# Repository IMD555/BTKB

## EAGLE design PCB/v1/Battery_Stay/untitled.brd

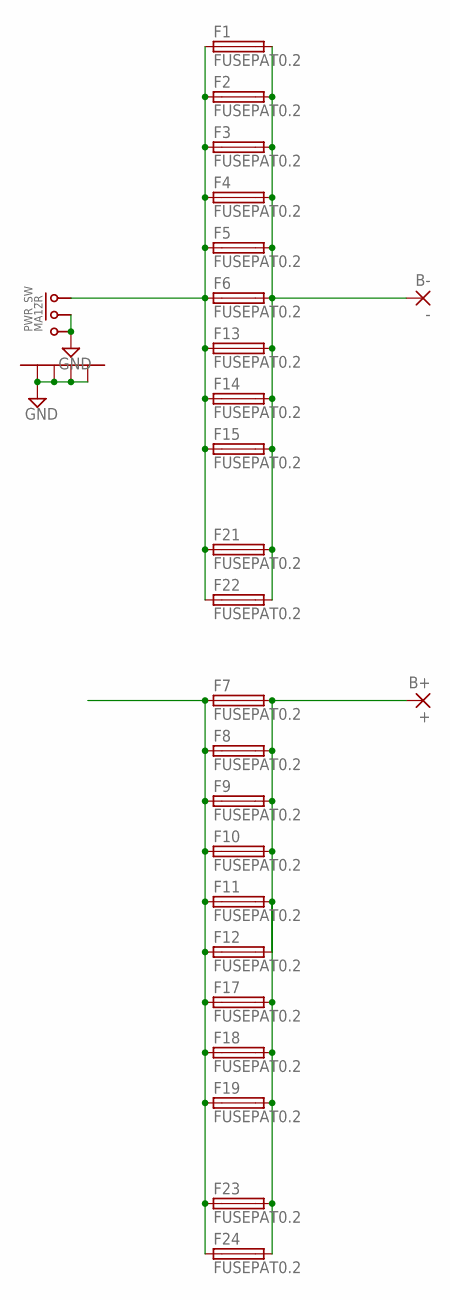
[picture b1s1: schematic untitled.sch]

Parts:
B+: +; SMD2,5-5
B-: -; SMD2,5-5
F1, F2, F3, F4, F5, F6, F7, F8, F9, F10, F11, F12, F13, F14, F15, F17, F18, F19, F21, F22, F23, F24: FUSEPAT0.2; FUSE_PAT1
PWR_SW: MA12R

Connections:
GND: PWR_SW.P$2 (2), PWR_SW.P$3 (3), PWR_SW.P$4, PWR_SW.P$5, PWR_SW.P$6, PWR_SW.P$7
unnamed: F1.P$1 (1), F2.P$1 (1), F3.P$1 (1), F4.P$1 (1), F5.P$1 (1), F6.P$1 (1), F13.P$1 (1), F14.P$1 (1), F15.P$1 (1), F21.P$1 (1), F22.P$1 (1), PWR_SW.P$1 (1)
unnamed: B-.1, F1.P$2 (2), F2.P$2 (2), F3.P$2 (2), F4.P$2 (2), F5.P$2 (2), F6.P$2 (2), F13.P$2 (2), F14.P$2 (2), F15.P$2 (2), F21.P$2 (2), F22.P$2 (2)
unnamed: F7.P$1 (1), F8.P$1 (1), F9.P$1 (1), F10.P$1 (1), F11.P$1 (1), F12.P$1 (1), F17.P$1 (1), F18.P$1 (1), F19.P$1 (1), F23.P$1 (1), F24.P$1 (1)
unnamed: B+.1, F7.P$2 (2), F8.P$2 (2), F9.P$2 (2), F10.P$2 (2), F11.P$2 (2), F12.P$2 (2), F17.P$2 (2), F18.P$2 (2), F19.P$2 (2), F23.P$2 (2), F24.P$2 (2)

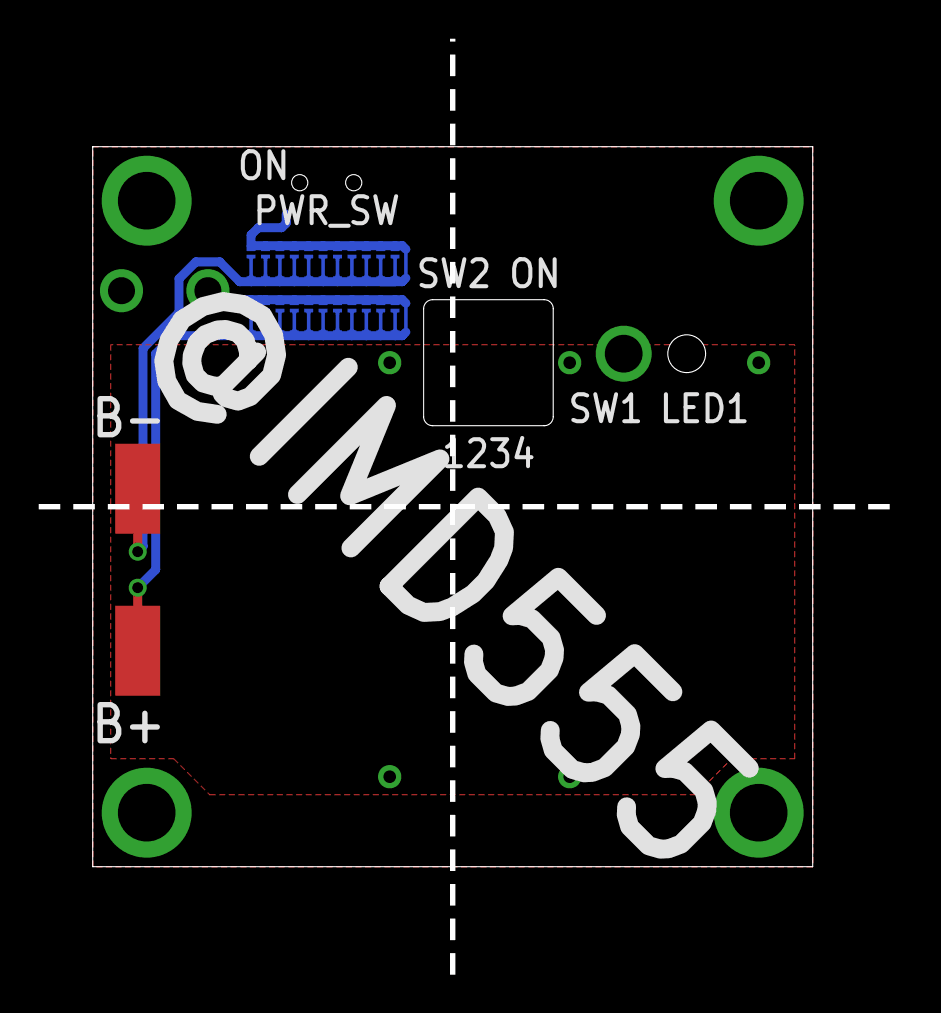
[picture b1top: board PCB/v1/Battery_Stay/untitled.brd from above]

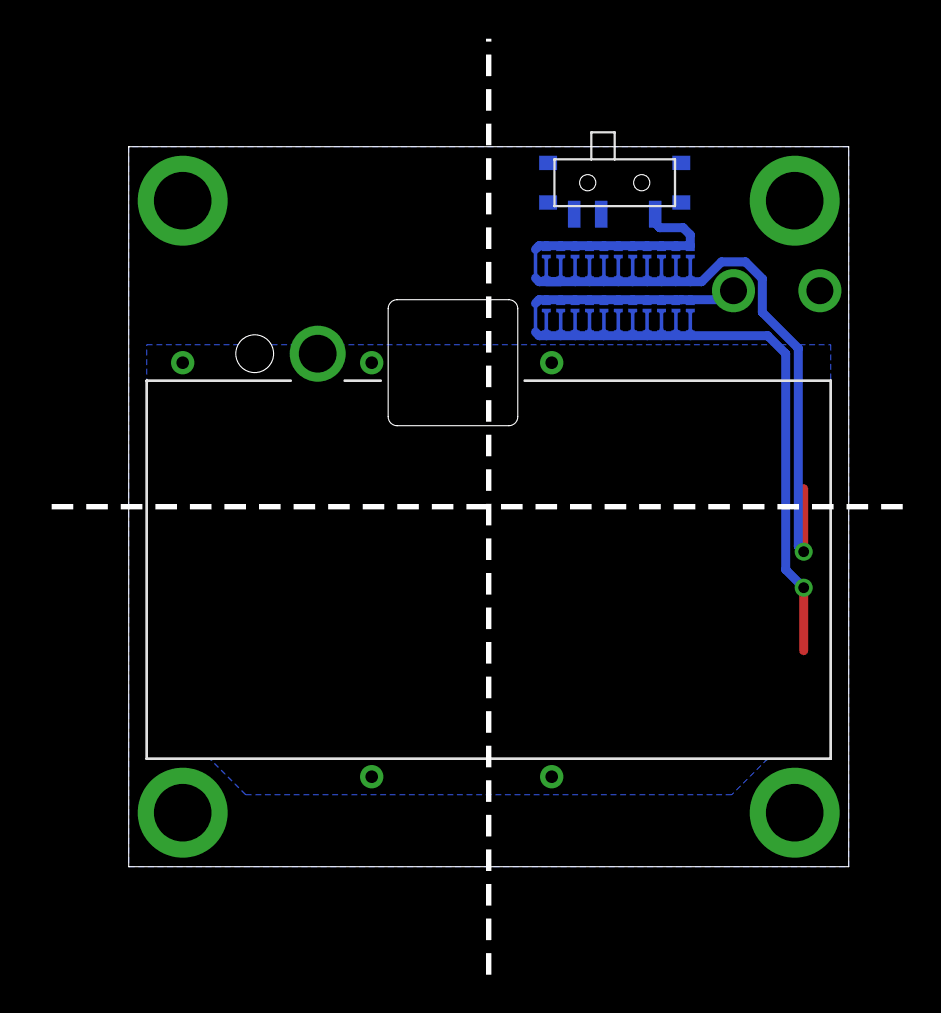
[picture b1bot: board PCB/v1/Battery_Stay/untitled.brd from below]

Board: 2 copper layers, 48.0 x 52.0 mm, 25 parts (23 on the bottom side), 5 nets.

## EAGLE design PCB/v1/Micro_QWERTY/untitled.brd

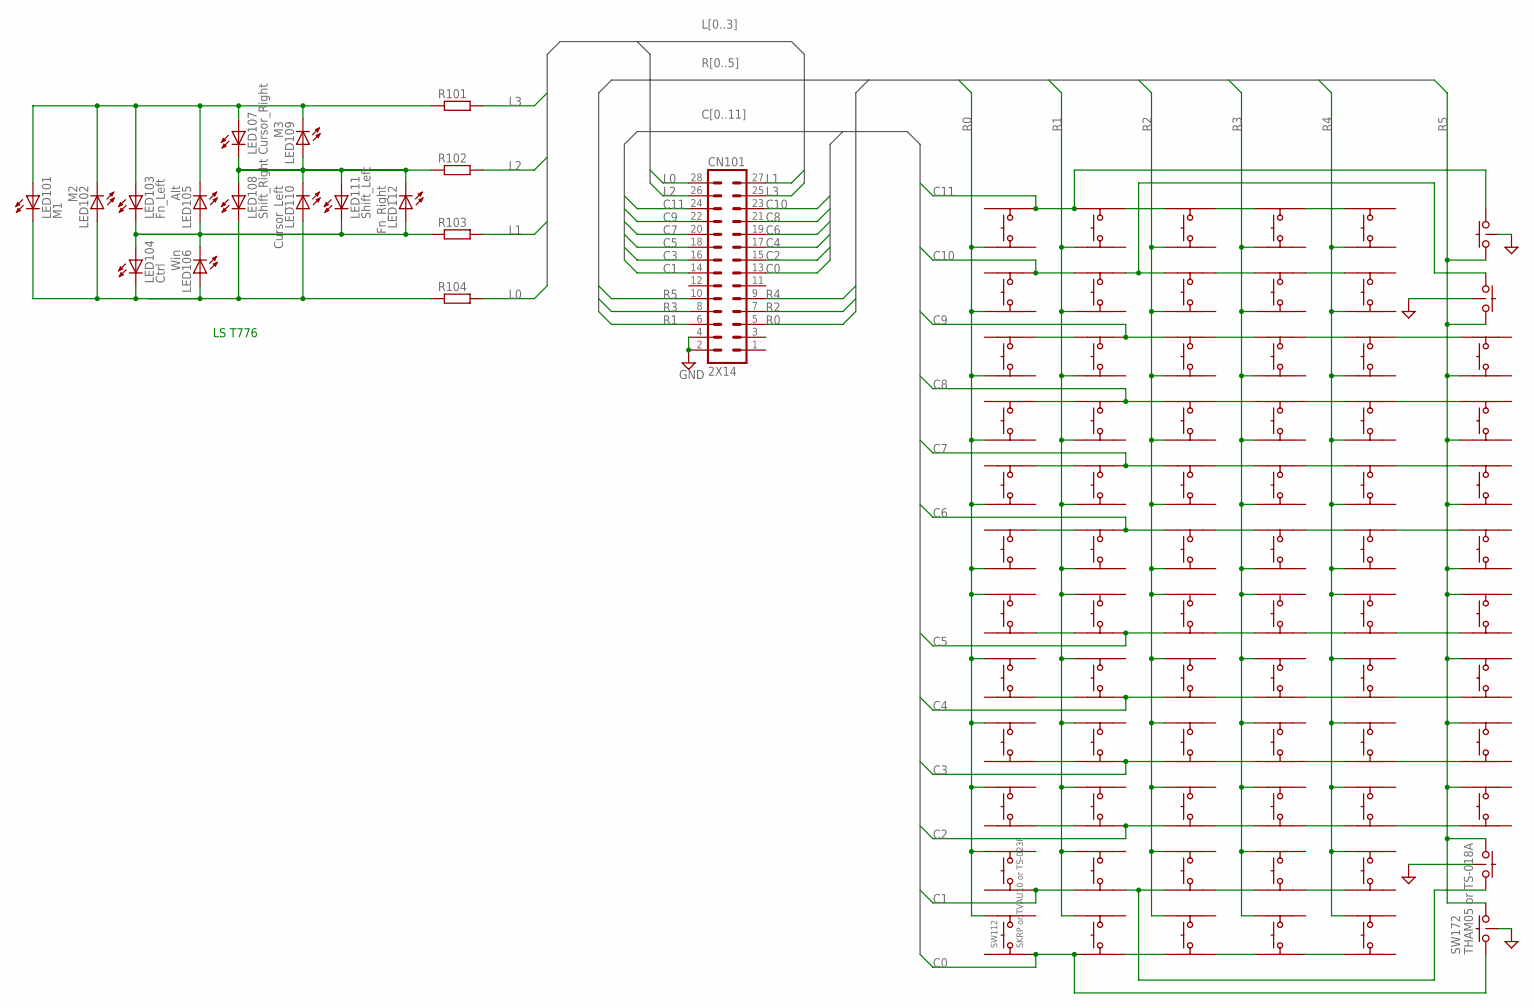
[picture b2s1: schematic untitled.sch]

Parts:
CN101: 2X14; 2MM_14X2
LED101: M1; P-LCC-2-TOPLED-RG
LED102: M2; P-LCC-2-TOPLED-RG
LED103: Fn_Left; P-LCC-2-TOPLED-RG
LED104: Ctrl; P-LCC-2-TOPLED-RG
LED105: Alt; P-LCC-2-TOPLED-RG
LED106: Win; P-LCC-2-TOPLED-RG
LED107: Cursor_Right; P-LCC-2-TOPLED-RG
LED108: Shift_Right; P-LCC-2-TOPLED-RG
LED109: M3; P-LCC-2-TOPLED-RG
LED110: Cursor_Left; P-LCC-2-TOPLED-RG
LED111: Shift_Left; P-LCC-2-TOPLED-RG
LED112: Fn_Right; P-LCC-2-TOPLED-RG
R101, R102, R103, R104: R-EU_R0402-SS; R0402-SS
SW101, SW102, SW103, SW104, SW105, SW106, SW107, SW108, SW109, SW110, SW111, SW113, SW114, SW115, SW116, SW117, SW118, SW119, SW120, SW121, SW122, SW123, SW124, SW125, SW126, SW127, SW128, SW129, SW130, SW131, SW132, SW133, SW134, SW135, SW136, SW137, SW138, SW139, SW140, SW141, SW142, SW143, SW144, SW145, SW146, SW147, SW148, SW149, SW150, SW151, SW152, SW153, SW154, SW155, SW156, SW157, SW158, SW159, SW160, SW163, SW164, SW165, SW166, SW167, SW168, SW169, SW170: SW_4PTVAU10-025; TVAU10-025
SW112: SKRP or TVAU10 or TS-023F; TVAU10-025
SW161, SW162, SW171: SW_WITH_EARTHX; THAM05
SW172: THAM05 or TS-018A; THAM05

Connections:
C0: CN101.13, SW112.P$2 (=A), SW124.P$1 (A), SW172.P$1
C1: CN101.14, SW111.P$2 (=A), SW123.P$1 (A)
C2: CN101.15, SW122.P$2 (=A), SW134.P$1 (A)
C3: CN101.16, SW121.P$2 (=A), SW133.P$1 (A)
C4: CN101.17, SW120.P$2 (=A), SW132.P$1 (A)
C5: CN101.18, SW119.P$2 (=A), SW131.P$1 (A)
C6: CN101.19, SW118.P$4 (=B), SW130.P$3 (B)
C7: CN101.20, SW117.P$4 (=B), SW129.P$3 (B)
C8: CN101.21, SW116.P$4 (=B), SW128.P$3 (B)
C9: CN101.22, SW115.P$4 (=B), SW127.P$3 (B)
C10: CN101.23, SW102.P$4 (=B), SW114.P$3 (B)
C11: CN101.24, SW101.P$4 (=B), SW113.P$3 (B), SW161.P$2
GND: CN101.2, CN101.4, SW161.S1, SW161.S2, SW161.S3, SW161.S4, SW161.S5, SW162.S1, SW162.S2, SW162.S3, SW162.S4, SW162.S5, SW171.S1, SW171.S2, SW171.S3, SW171.S4, SW171.S5, SW172.S1, SW172.S2, SW172.S3, SW172.S4, SW172.S5
L0: CN101.28, R104.2
L1: CN101.27, R103.2
L2: CN101.26, R102.2
L3: CN101.25, R101.2
unnamed: LED107.C, LED108.A, LED109.A, LED110.C, LED111.A, LED112.C, R102.1
unnamed: LED101.A, LED102.C, LED103.A, LED105.C, LED107.A, LED109.C, R101.1
unnamed: LED103.C, LED104.A, LED105.A, LED106.C, LED111.C, LED112.A, R103.1
unnamed: LED101.C, LED102.A, LED104.C, LED106.A, LED108.C, LED110.A, R104.1
unnamed: SW123.P$2 (=A), SW135.P$1 (A), SW171.P$2
unnamed: SW113.P$4 (=B), SW125.P$3 (B)
unnamed: SW114.P$4 (=B), SW126.P$3 (B), SW162.P$1
unnamed: SW106.P$4 (=B), SW118.P$3 (B)
unnamed: SW130.P$4 (=B), SW142.P$3 (B)
unnamed: SW154.P$4 (=B), SW166.P$3 (B)
unnamed: SW142.P$4 (=B), SW154.P$3 (B)
unnamed: SW105.P$4 (=B), SW117.P$3 (B)
unnamed: SW129.P$4 (=B), SW141.P$3 (B)
unnamed: SW153.P$4 (=B), SW165.P$3 (B)
unnamed: SW141.P$4 (=B), SW153.P$3 (B)
unnamed: SW104.P$4 (=B), SW116.P$3 (B)
unnamed: SW128.P$4 (=B), SW140.P$3 (B)
unnamed: SW152.P$4 (=B), SW164.P$3 (B)
unnamed: SW140.P$4 (=B), SW152.P$3 (B)
unnamed: SW103.P$4 (=B), SW115.P$3 (B)
unnamed: SW127.P$4 (=B), SW139.P$3 (B)
unnamed: SW151.P$4 (=B), SW163.P$3 (B)
unnamed: SW139.P$4 (=B), SW151.P$3 (B)
unnamed: SW126.P$4 (=B), SW138.P$3 (B)
unnamed: SW138.P$4 (=B), SW150.P$3 (B)
unnamed: SW125.P$4 (=B), SW137.P$3 (B)
unnamed: SW137.P$4 (=B), SW149.P$3 (B)
unnamed: SW107.P$2 (=A), SW119.P$1 (A)
unnamed: SW131.P$2 (=A), SW143.P$1 (A)
unnamed: SW155.P$2 (=A), SW167.P$1 (A)
unnamed: SW143.P$2 (=A), SW155.P$1 (A)
unnamed: SW108.P$2 (=A), SW120.P$1 (A)
unnamed: SW132.P$2 (=A), SW144.P$1 (A)
unnamed: SW156.P$2 (=A), SW168.P$1 (A)
unnamed: SW144.P$2 (=A), SW156.P$1 (A)
unnamed: SW109.P$2 (=A), SW121.P$1 (A)
unnamed: SW133.P$2 (=A), SW145.P$1 (A)
unnamed: SW157.P$2 (=A), SW169.P$1 (A)
unnamed: SW145.P$2 (=A), SW157.P$1 (A)
unnamed: SW110.P$2 (=A), SW122.P$1 (A)
unnamed: SW134.P$2 (=A), SW146.P$1 (A)
unnamed: SW158.P$2 (=A), SW170.P$1 (A)
unnamed: SW146.P$2 (=A), SW158.P$1 (A)
unnamed: SW135.P$2 (=A), SW147.P$1 (A)
unnamed: SW147.P$2 (=A), SW159.P$1 (A)
unnamed: SW124.P$2 (=A), SW136.P$1 (A)
unnamed: SW136.P$2 (=A), SW148.P$1 (A)
unnamed: SW148.P$2 (=A), SW160.P$1 (A)
R0: CN101.5, SW101.P$1 (A), SW102.P$1 (A), SW103.P$1 (A), SW104.P$1 (A), SW105.P$1 (A), SW106.P$1 (A), SW107.P$3 (B), SW108.P$3 (B), SW109.P$3 (B), SW110.P$3 (B), SW111.P$3 (B), SW112.P$3 (B)
R1: CN101.6, SW113.P$1 (A), SW114.P$1 (A), SW115.P$1 (A), SW116.P$1 (A), SW117.P$1 (A), SW118.P$1 (A), SW119.P$3 (B), SW120.P$3 (B), SW121.P$3 (B), SW122.P$3 (B), SW123.P$3 (B), SW124.P$3 (B)
R2: CN101.7, SW125.P$1 (A), SW126.P$1 (A), SW127.P$1 (A), SW128.P$1 (A), SW129.P$1 (A), SW130.P$1 (A), SW131.P$3 (B), SW132.P$3 (B), SW133.P$3 (B), SW134.P$3 (B), SW135.P$3 (B), SW136.P$3 (B)
R3: CN101.8, SW137.P$1 (A), SW138.P$1 (A), SW139.P$1 (A), SW140.P$1 (A), SW141.P$1 (A), SW142.P$1 (A), SW143.P$3 (B), SW144.P$3 (B), SW145.P$3 (B), SW146.P$3 (B), SW147.P$3 (B), SW148.P$3 (B)
R4: CN101.9, SW149.P$1 (A), SW150.P$1 (A), SW151.P$1 (A), SW152.P$1 (A), SW153.P$1 (A), SW154.P$1 (A), SW155.P$3 (B), SW156.P$3 (B), SW157.P$3 (B), SW158.P$3 (B), SW159.P$3 (B), SW160.P$3 (B)
R5: CN101.10, SW161.P$1, SW162.P$2, SW163.P$1 (A), SW164.P$1 (A), SW165.P$1 (A), SW166.P$1 (A), SW167.P$3 (B), SW168.P$3 (B), SW169.P$3 (B), SW170.P$3 (B), SW171.P$1, SW172.P$2

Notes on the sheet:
LS T776

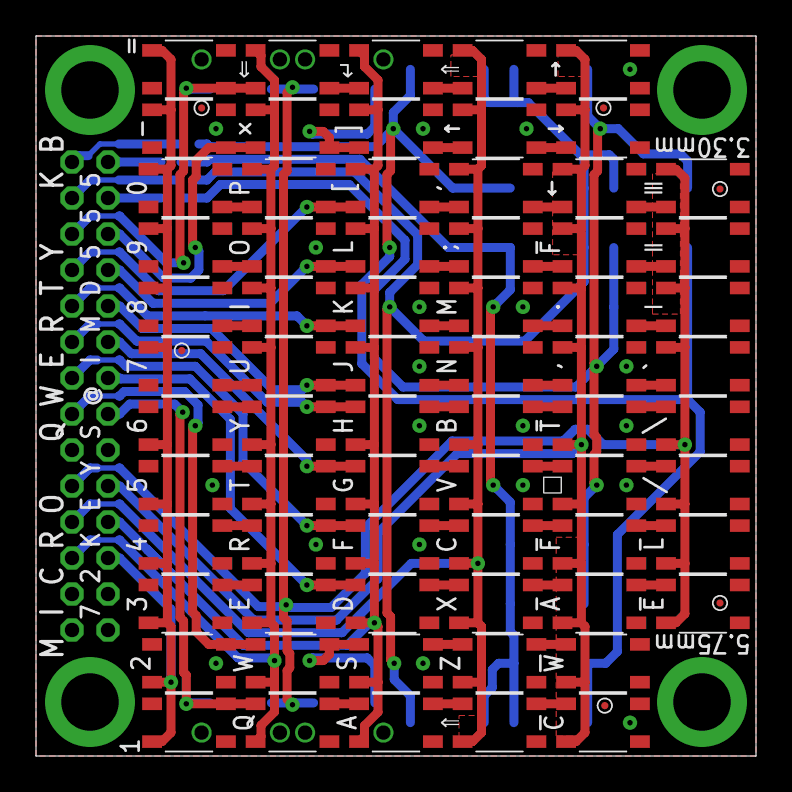
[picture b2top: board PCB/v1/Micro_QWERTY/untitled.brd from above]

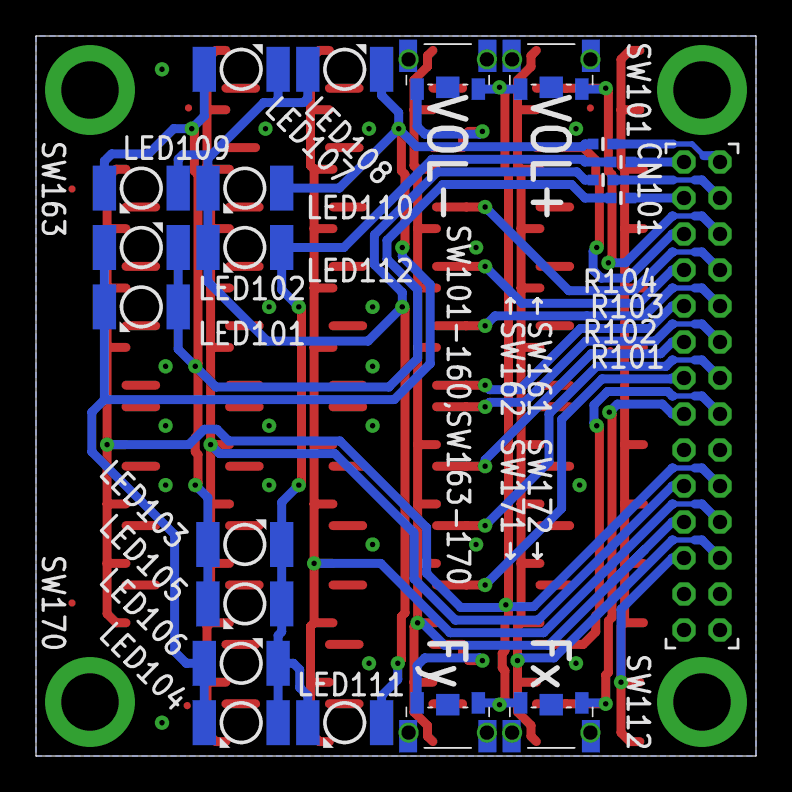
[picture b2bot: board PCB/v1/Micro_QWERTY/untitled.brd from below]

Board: 2 copper layers, 40.0 x 40.0 mm, 97 parts (22 on the bottom side), 71 nets.

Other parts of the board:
U$1, U$4, U$5, U$6, U$7, U$8: PCB_CHECK
U$2, U$3: RULER-S

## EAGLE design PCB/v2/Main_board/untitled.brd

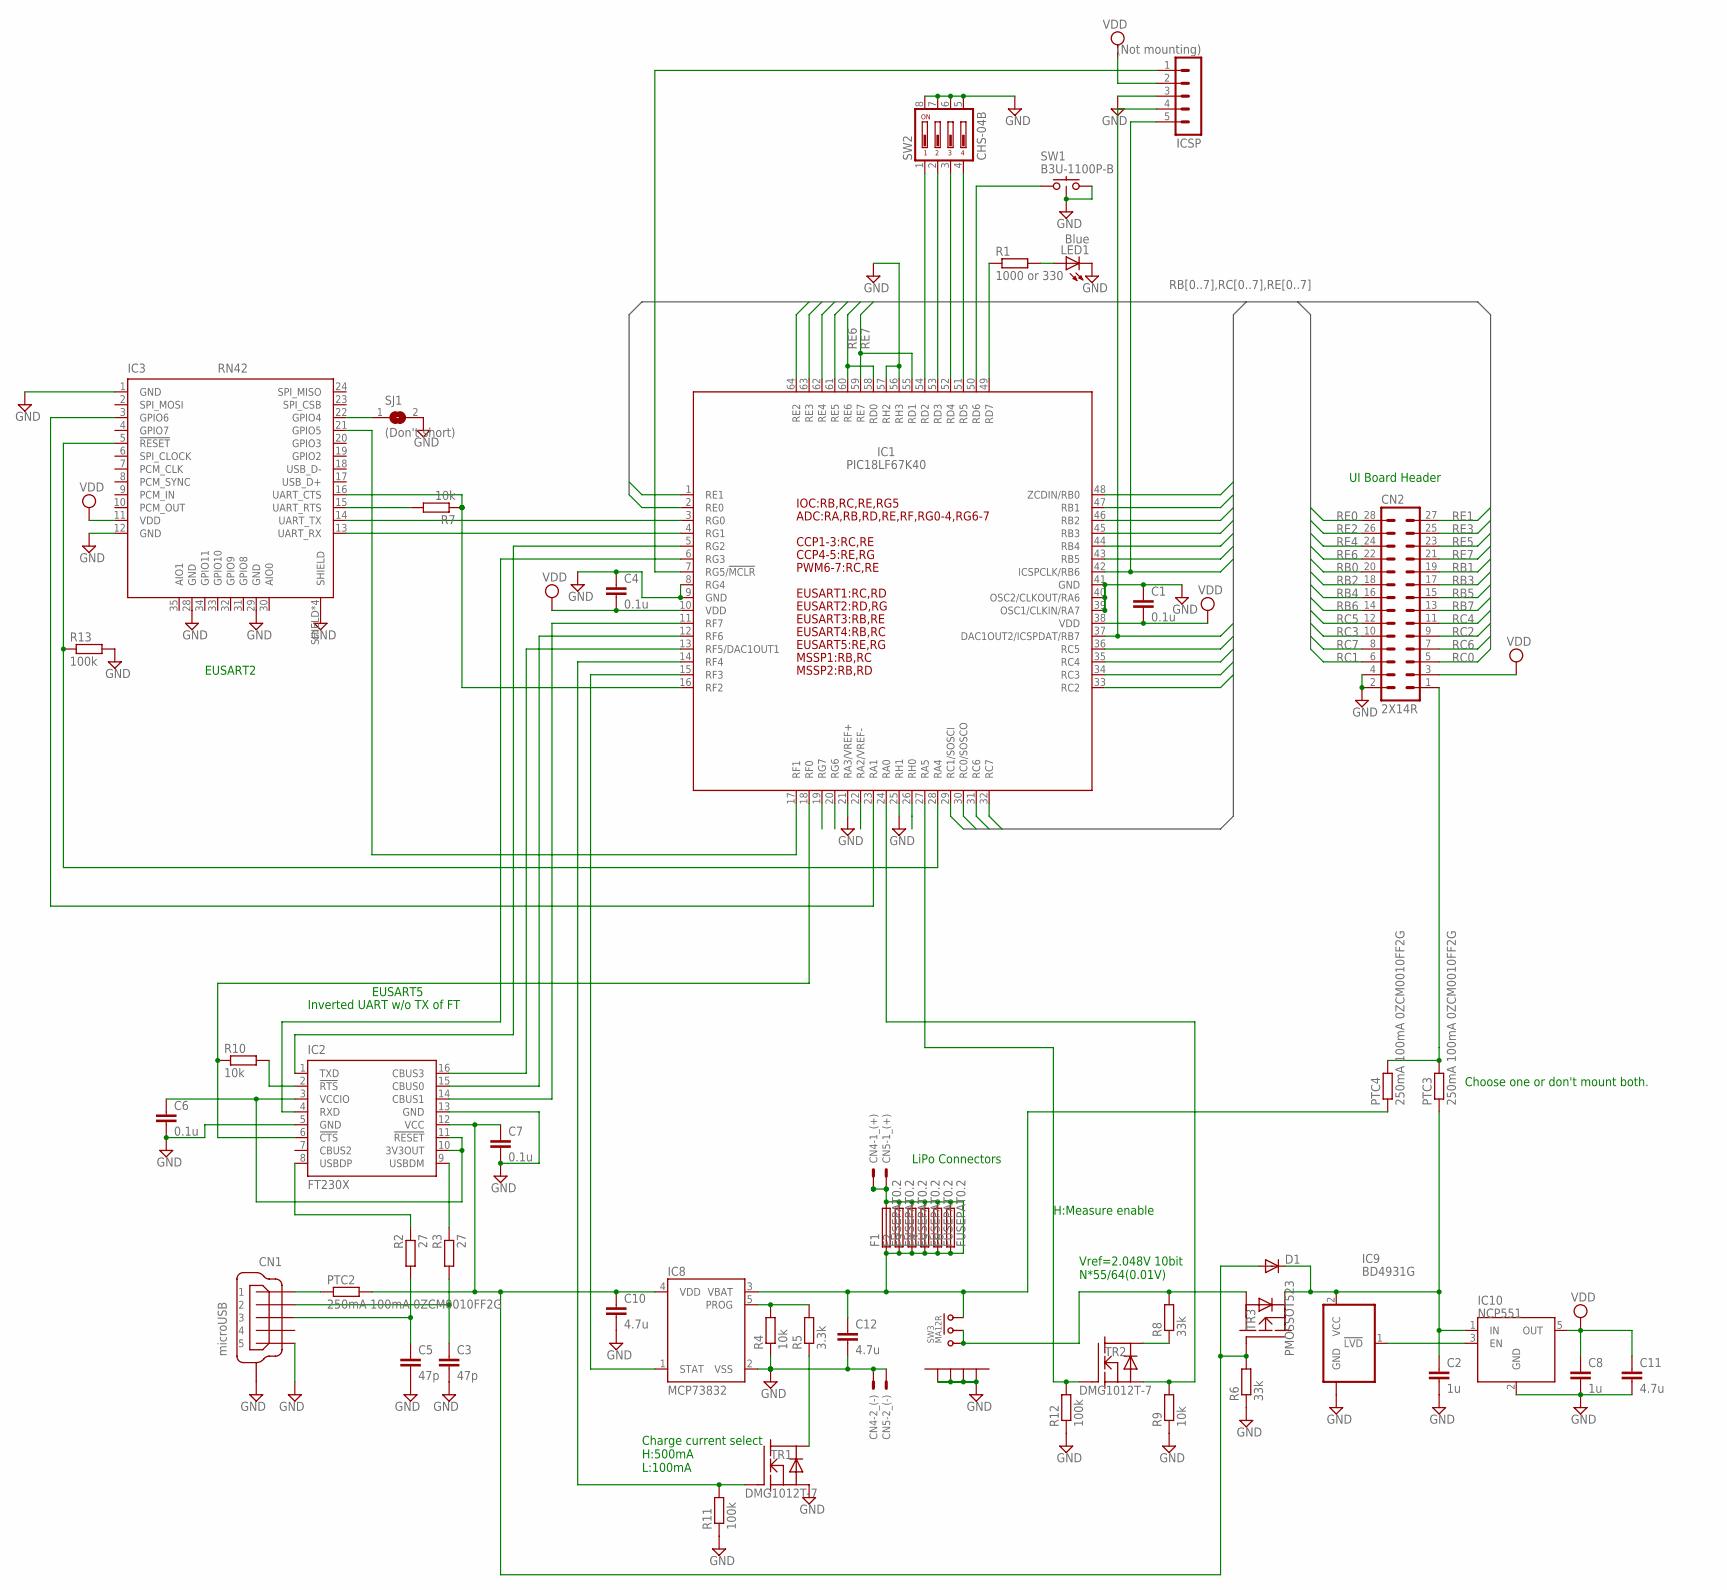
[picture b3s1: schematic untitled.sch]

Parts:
C1, C4, C6, C7: 0.1u; C0402-SS
C2, C8: 1u; C0805
C3, C5: 47p; C0402-SS
C10, C11, C12: 4.7u; C0805
CN1: microUSB; 10118194-0001LF
CN2: 2X14R; 2MM_14X2_R
CN4, CN5: 2P_(POWER)PH_S; PH-2_S
D1: DIODE-VMN2; VMN2
F1, F2, F3, F4, F5, F6: FUSEPAT0.2; FUSE_PAT1
IC1: PIC18LF67K40; TQFP64-10X10
IC2: FT230X; SSOP16
IC3: RN42; RN-42
IC8: MCP73832; SOT23-5L
IC9: BD4931G; SOT23-5L
IC10: NCP551; SOT23-5L
ICSP: (Not mounting); MA05-1
LED1: Blue; CHIP-LED1005
PTC2, PTC3, PTC4: 250mA 100mA 0ZCM0010FF2G; R0603
R1: 1000 or 330; R0402-SS
R2, R3: 27; R0402-SS
R4, R7, R9, R10: 10k; R0402-SS
R5: 3.3k; R0402-SS
R6, R8: 33k; R0402-SS
R11, R12, R13: 100k; R0402-SS
SJ1: (Don't short); SJ
SW1: B3U-1100P-B
SW2: CHS-04B
SW3: MA12R
TR1, TR2: DMG1012T-7; SOT523
TR3: PMOSSOT523; SOT523

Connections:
GND: C1.1, C2.2, C3.2, C4.1, C5.2, C6.2, C7.2, C8.2, C10.2, C11.2, C12.2, CN1.P$5 (5), CN1.P$6 (S), CN1.P$7 (S), CN1.S1 (S), CN1.S2 (S), CN1.S3 (S), CN1.S4 (S), CN1.S5 (S), CN1.S6 (S), CN1.S7 (S), CN1.S8 (S), CN1.S9 (S), CN1.S10 (S), CN2.2, CN2.4, CN4.2, CN5.2, IC1.8 (RG4), IC1.9 (GND), IC1.21 (RA3/VREF+), IC1.25 (RH1), IC1.39 (OSC1/CLKIN/RA7), IC1.40 (OSC2/CLKOUT/RA6), IC1.41 (GND), IC1.56 (RH3), IC1.57 (RH2), IC2.5 (GND), IC2.13 (GND), IC3.1 (GND), IC3.12 (GND), IC3.28 (GND), IC3.29 (GND), IC3.SHIELD, IC3.SHIELD@1 (SHIELD), IC3.SHIELD@2 (SHIELD), IC3.SHIELD@3 (SHIELD), IC8.2 (VSS), IC9.3 (GND), IC10.2 (GND), ICSP.3, LED1.C, R4.1, R6.1, R9.1, R11.1, R12.1, R13.2, SJ1.2, SW1.P$2, SW1.P$3, SW2.5, SW2.6, SW2.7, SW2.8, SW3.P$4, SW3.P$5, SW3.P$6, SW3.P$7, TR1.2 (S)
unnamed: IC1.4 (RG1), IC3.13 (UART_RX)
unnamed: IC1.5 (RG2), IC2.1 (TXD)
unnamed: IC1.3 (RG0), IC3.14 (UART_TX)
unnamed: C5.1, CN1.P$3 (3), R2.2
unnamed: C3.1, CN1.P$2 (2), R3.2
unnamed: IC1.6 (RG3), IC2.4 (RXD)
unnamed: CN2.1, PTC3.2, PTC4.2
unnamed: C7.1, C10.1, D1.A, IC2.12 (VCC), IC8.4 (VDD), PTC2.2, R6.2, TR3.1 (G)
unnamed: IC1.15 (RF3), IC8.1 (STAT)
unnamed: C12.1, CN4.1, CN5.1, F1.P$1 (1), F1.P$2 (2), F2.P$1 (1), F2.P$2 (2), F3.P$1 (1), F3.P$2 (2), F4.P$1 (1), F4.P$2 (2), F5.P$1 (1), F5.P$2 (2), F6.P$1 (1), F6.P$2 (2), IC8.3 (VBAT), PTC4.1, SW3.P$1 (1)
unnamed: R8.2, SW3.P$2 (2), SW3.P$3 (3), TR3.3 (D)
unnamed: IC1.7 (RG5/!MCLR), ICSP.1
unnamed: CN1.P$1 (1), PTC2.1
unnamed: IC1.54 (RD2), SW2.1
unnamed: IC1.52 (RD4), SW2.3
unnamed: IC1.51 (RD5), SW2.4
unnamed: IC1.49 (RD7), R1.1
unnamed: IC1.28 (RA4), IC3.5 (!RESET), R13.1
unnamed: LED1.A, R1.2
unnamed: C6.1, IC2.3 (VCCIO), IC2.10 (3V3OUT), IC2.11 (!RESET)
unnamed: IC1.50 (RD6), SW1.P$1
unnamed: IC2.9 (USBDM), R3.1
unnamed: IC1.53 (RD3), SW2.2
unnamed: IC2.8 (USBDP), R2.1
unnamed: IC1.12 (RF6), IC2.15 (CBUS0)
unnamed: IC1.13 (RF5/DAC1OUT1), IC2.16 (CBUS3)
unnamed: IC8.5 (PROG), R4.2, R5.2
unnamed: IC1.27 (RA5), R12.2, TR2.1 (G)
unnamed: IC1.16 (RF2), IC3.16 (UART_CTS), R7.1
unnamed: IC1.14 (RF4), R11.2, TR1.1 (G)
unnamed: IC3.15 (UART_RTS), R7.2
unnamed: IC1.11 (RF7), IC2.14 (CBUS1)
unnamed: IC2.2 (!RTS), R10.2
unnamed: IC1.18 (RF0), IC2.6 (!CTS), R10.1
unnamed: IC1.17 (RF1), IC3.21 (GPIO5)
unnamed: IC3.22 (GPIO4), SJ1.1
unnamed: IC9.1 (!LVD!), IC10.3 (EN)
unnamed: R5.1, TR1.3 (D)
unnamed: R8.1, TR2.3 (D)
unnamed: IC1.24 (RA0), R9.2, TR2.2 (S)
unnamed: IC1.23 (RA1), IC3.3 (GPIO6)
RB0: CN2.20, IC1.48 (ZCDIN/RB0)
RB1: CN2.19, IC1.47 (RB1)
RB2: CN2.18, IC1.46 (RB2)
RB3: CN2.17, IC1.45 (RB3)
RB4: CN2.16, IC1.44 (RB4)
RB5: CN2.15, IC1.43 (RB5)
RB6: CN2.14, IC1.42 (ICSPCLK/RB6), ICSP.5
RB7: CN2.13, IC1.37 (DAC1OUT2/ICSPDAT/RB7), ICSP.4
RC0: CN2.5, IC1.30 (RC0/SOSCO)
RC1: CN2.6, IC1.29 (RC1/SOSCI)
RC2: CN2.9, IC1.33 (RC2)
RC3: CN2.10, IC1.34 (RC3)
RC4: CN2.11, IC1.35 (RC4)
RC5: CN2.12, IC1.36 (RC5)
RC6: CN2.7, IC1.31 (RC6)
RC7: CN2.8, IC1.32 (RC7)
RE0: CN2.28, IC1.2 (RE0)
RE1: CN2.27, IC1.1 (RE1)
RE2: CN2.26, IC1.64 (RE2)
RE3: CN2.25, IC1.63 (RE3)
RE4: CN2.24, IC1.62 (RE4)
RE5: CN2.23, IC1.61 (RE5)
RE6: CN2.22, IC1.58 (RD0), IC1.60 (RE6)
RE7: CN2.21, IC1.55 (RD1), IC1.59 (RE7)
VBAT: C2.1, D1.C, IC9.2 (VCC), IC10.1 (IN), PTC3.1, TR3.2 (S)
VDD: C1.2, C4.2, C8.1, C11.1, CN2.3, IC1.10 (VDD), IC1.38 (VDD), IC3.11 (VDD), IC10.5 (OUT), ICSP.2

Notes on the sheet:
Charge current select H:500mA L:100mA
H:Measure enable
LiPo Connectors
UI Board Header
Inverted UART w/o TX of FT
Vref=2.048V 10bit N*55/64(0.01V)
EUSART2
EUSART5
Choose one or don't mount both.

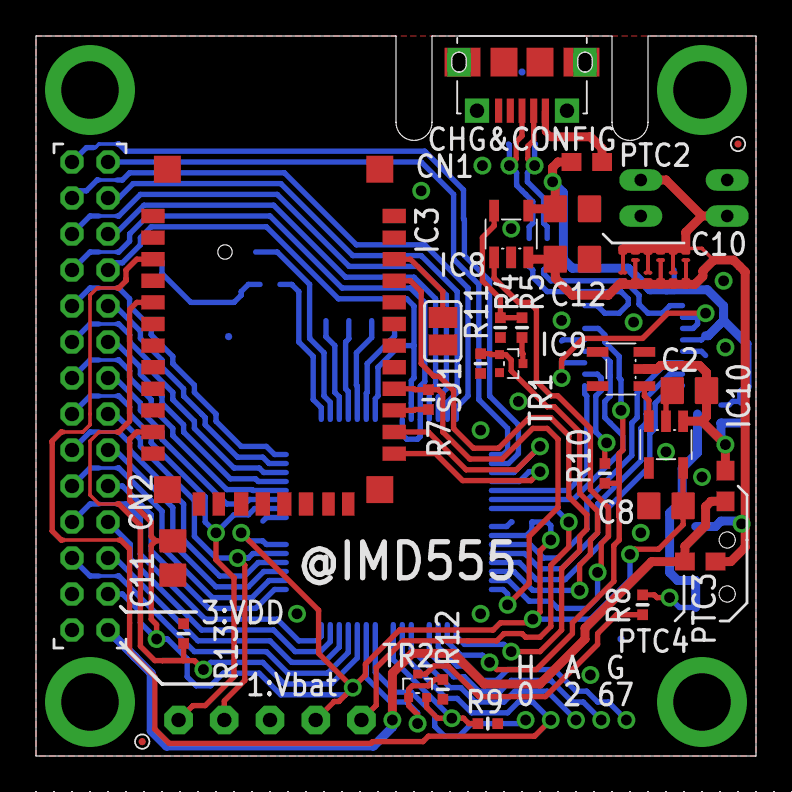
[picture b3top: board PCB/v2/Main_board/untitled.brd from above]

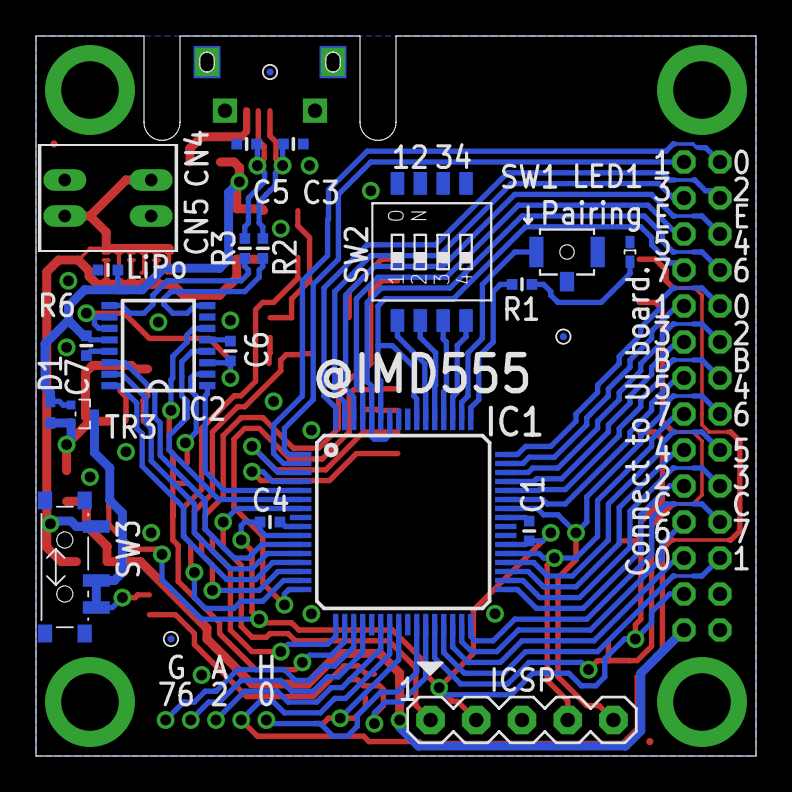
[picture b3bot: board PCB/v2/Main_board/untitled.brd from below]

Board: 2 copper layers, 40.0 x 40.0 mm, 60 parts (25 on the bottom side), 68 nets.

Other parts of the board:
U$1, U$3, U$6, U$8, U$9: PCB_CHECK
U$2: RULER
U$4: RULER-S

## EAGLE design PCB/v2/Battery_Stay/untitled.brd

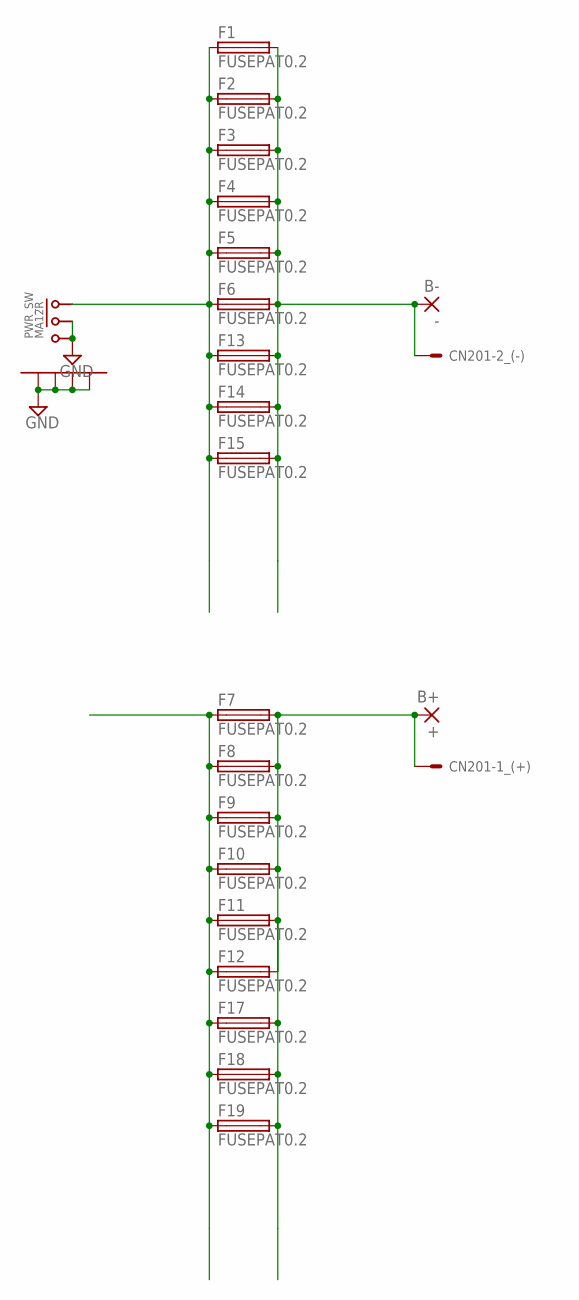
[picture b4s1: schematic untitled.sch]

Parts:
B+: +; SMD2,5-5
B-: -; SMD2,5-5
CN201: 2P_(POWER)53048; 53048-0210
F1, F2, F3, F4, F5, F6, F7, F8, F9, F10, F11, F12, F13, F14, F15, F17, F18, F19: FUSEPAT0.2; FUSE_PAT1
PWR_SW: MA12R

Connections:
GND: PWR_SW.P$2 (2), PWR_SW.P$3 (3), PWR_SW.P$4, PWR_SW.P$5, PWR_SW.P$6, PWR_SW.P$7
unnamed: F1.P$1 (1), F2.P$1 (1), F3.P$1 (1), F4.P$1 (1), F5.P$1 (1), F6.P$1 (1), F13.P$1 (1), F14.P$1 (1), F15.P$1 (1), PWR_SW.P$1 (1)
unnamed: B-.1, CN201.2, F1.P$2 (2), F2.P$2 (2), F3.P$2 (2), F4.P$2 (2), F5.P$2 (2), F6.P$2 (2), F13.P$2 (2), F14.P$2 (2), F15.P$2 (2)
unnamed: F7.P$1 (1), F8.P$1 (1), F9.P$1 (1), F10.P$1 (1), F11.P$1 (1), F12.P$1 (1), F17.P$1 (1), F18.P$1 (1), F19.P$1 (1)
unnamed: B+.1, CN201.1, F7.P$2 (2), F8.P$2 (2), F9.P$2 (2), F10.P$2 (2), F11.P$2 (2), F12.P$2 (2), F17.P$2 (2), F18.P$2 (2), F19.P$2 (2)

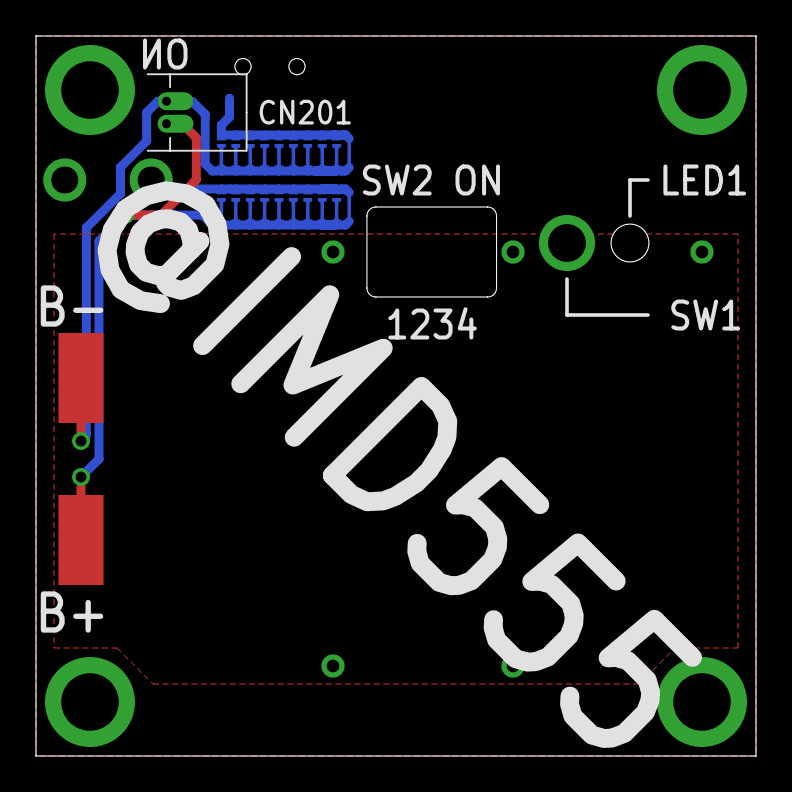
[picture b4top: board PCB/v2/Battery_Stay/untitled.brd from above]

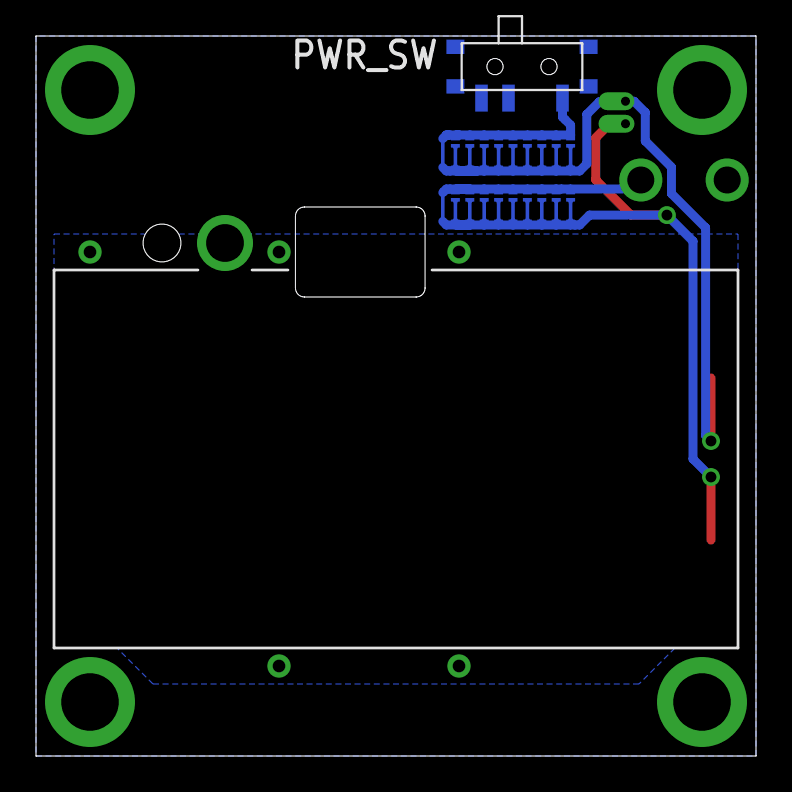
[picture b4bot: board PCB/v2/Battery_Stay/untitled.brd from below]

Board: 2 copper layers, 40.0 x 40.0 mm, 22 parts (19 on the bottom side), 5 nets.

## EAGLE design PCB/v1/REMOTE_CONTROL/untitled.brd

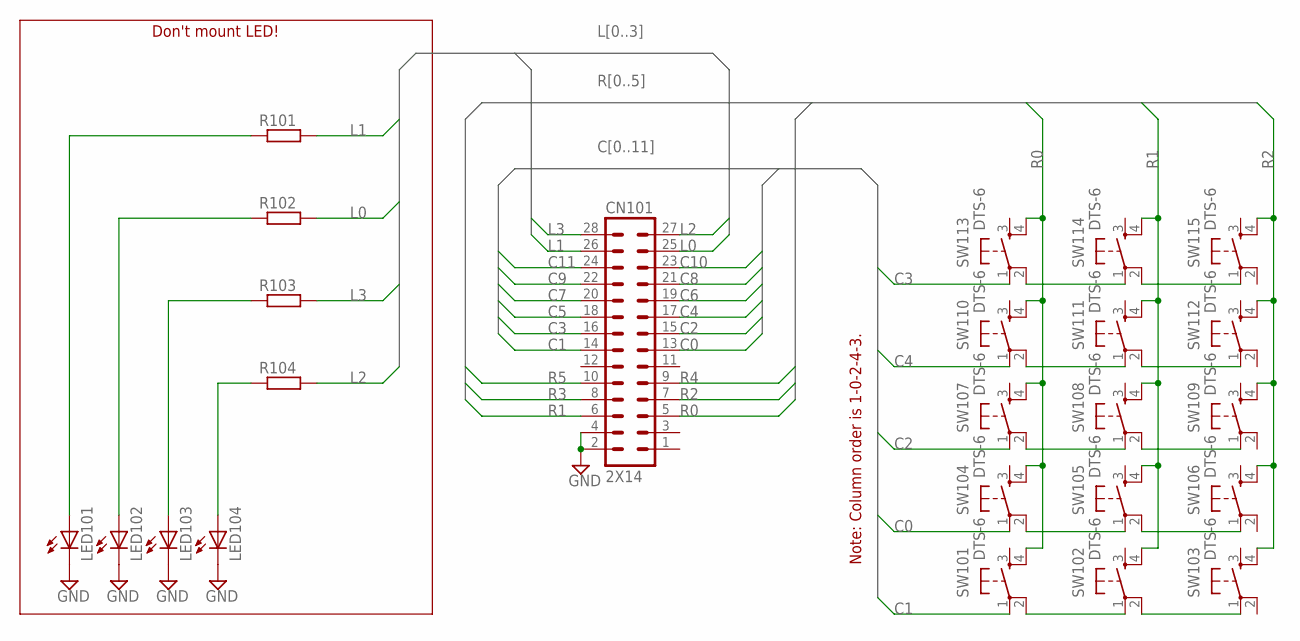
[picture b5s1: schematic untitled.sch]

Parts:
CN101: 2X14; 2MM_14X2
LED101, LED102, LED103, LED104: LEDP-LCC-2-BACK; P-LCC-2-TOPLED-RG
R101, R102, R103, R104: R-EU_R0402-SS; R0402-SS
SW101, SW102, SW103, SW104, SW105, SW106, SW107, SW108, SW109, SW110, SW111, SW112, SW113, SW114, SW115: DTS-6

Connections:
C0: CN101.13, SW104.1
C1: CN101.14, SW101.1
C2: CN101.15, SW107.1
C3: CN101.16, SW113.1
C4: CN101.17, SW110.1
C5: CN101.18
C6: CN101.19
C7: CN101.20
C8: CN101.21
C9: CN101.22
C10: CN101.23
C11: CN101.24
GND: CN101.2, CN101.4, LED101.C, LED102.C, LED103.C, LED104.C
L0: CN101.25, R102.2
L1: CN101.26, R101.2
L2: CN101.27, R104.2
L3: CN101.28, R103.2
unnamed: LED101.A, R101.1
unnamed: SW114.2, SW115.1
unnamed: LED102.A, R102.1
unnamed: SW111.2, SW112.1
unnamed: SW108.2, SW109.1
unnamed: LED103.A, R103.1
unnamed: SW102.2, SW103.1
unnamed: SW105.2, SW106.1
unnamed: LED104.A, R104.1
unnamed: SW110.2, SW111.1
unnamed: SW107.2, SW108.1
unnamed: SW104.2, SW105.1
unnamed: SW101.2, SW102.1
unnamed: SW113.2, SW114.1
R0: CN101.5, SW101.4, SW104.4, SW107.4, SW110.4, SW113.4
R1: CN101.6, SW102.4, SW105.4, SW108.4, SW111.4, SW114.4
R2: CN101.7, SW103.4, SW106.4, SW109.4, SW112.4, SW115.4
R3: CN101.8
R4: CN101.9
R5: CN101.10

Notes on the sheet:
Note: Column order is 1-0-2-4-3.
Don't mount LED!

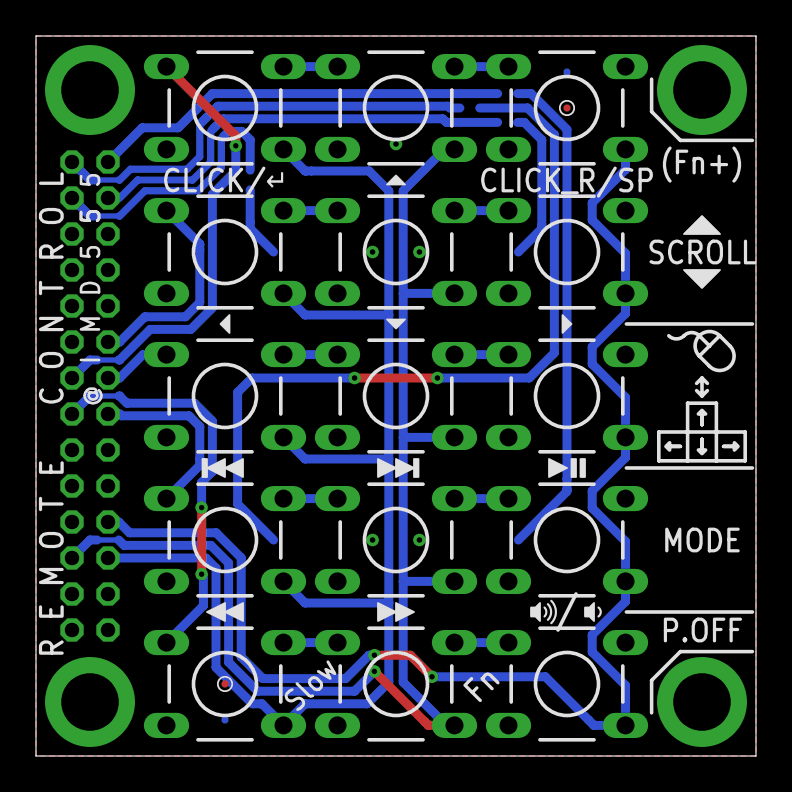
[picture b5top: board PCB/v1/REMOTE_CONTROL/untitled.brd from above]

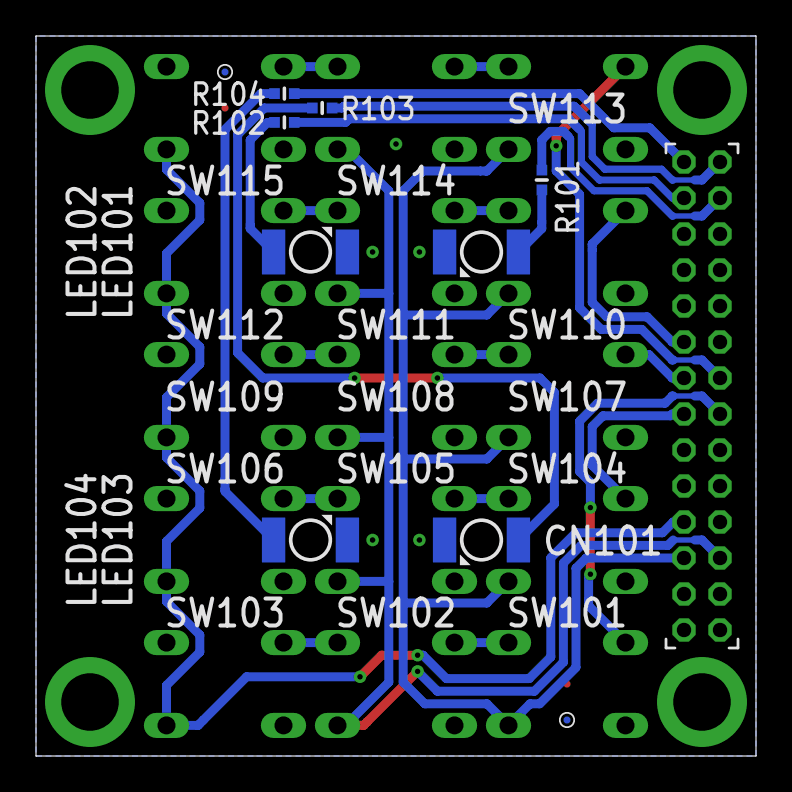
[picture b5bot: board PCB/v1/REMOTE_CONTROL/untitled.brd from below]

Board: 2 copper layers, 40.0 x 40.0 mm, 31 parts (12 on the bottom side), 27 nets.

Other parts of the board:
U$1, U$4, U$6, U$7: PCB_CHECK
U$2, U$3, U$5: RULER-S
